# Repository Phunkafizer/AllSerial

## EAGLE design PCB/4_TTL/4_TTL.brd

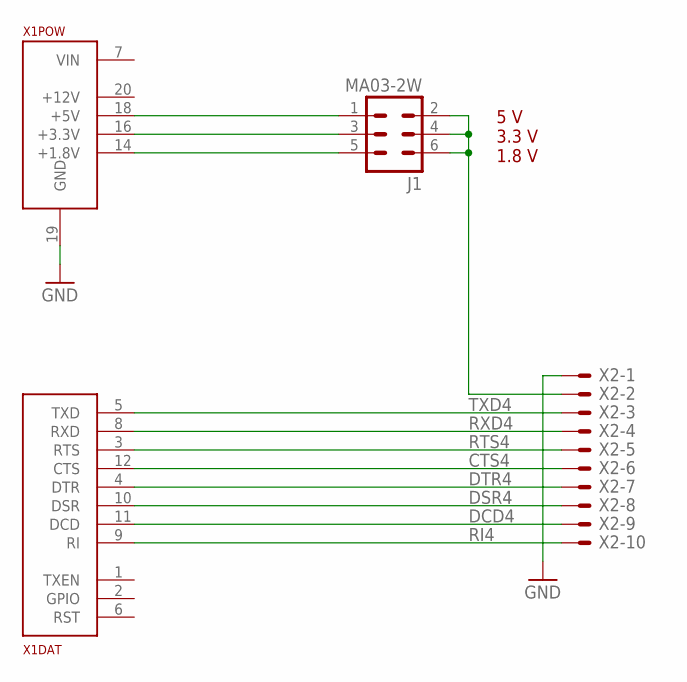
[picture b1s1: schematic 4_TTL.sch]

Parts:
J1: MA03-2W
X1: ALLSERIALD; DAUGHTER-THT
X2: AKL18X-10W; AKL182-10

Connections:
CTS4: X1.12 (CTS), X2.P$6
DCD4: X1.11 (DCD), X2.P$9
DSR4: X1.10 (DSR), X2.P$8
DTR4: X1.4 (DTR), X2.P$7
GND: X1.19 (GND), X2.P$1
unnamed: J1.2, J1.4, J1.6, X2.P$2
unnamed: J1.5, X1.14 (+1.8V)
unnamed: J1.3, X1.16 (+3.3V)
unnamed: J1.1, X1.18 (+5V)
RI4: X1.9 (RI), X2.P$10
RTS4: X1.3 (RTS), X2.P$5
RXD4: X1.8 (RXD), X2.P$4
TXD4: X1.5 (TXD), X2.P$3

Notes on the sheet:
5 V 3.3 V 1.8 V

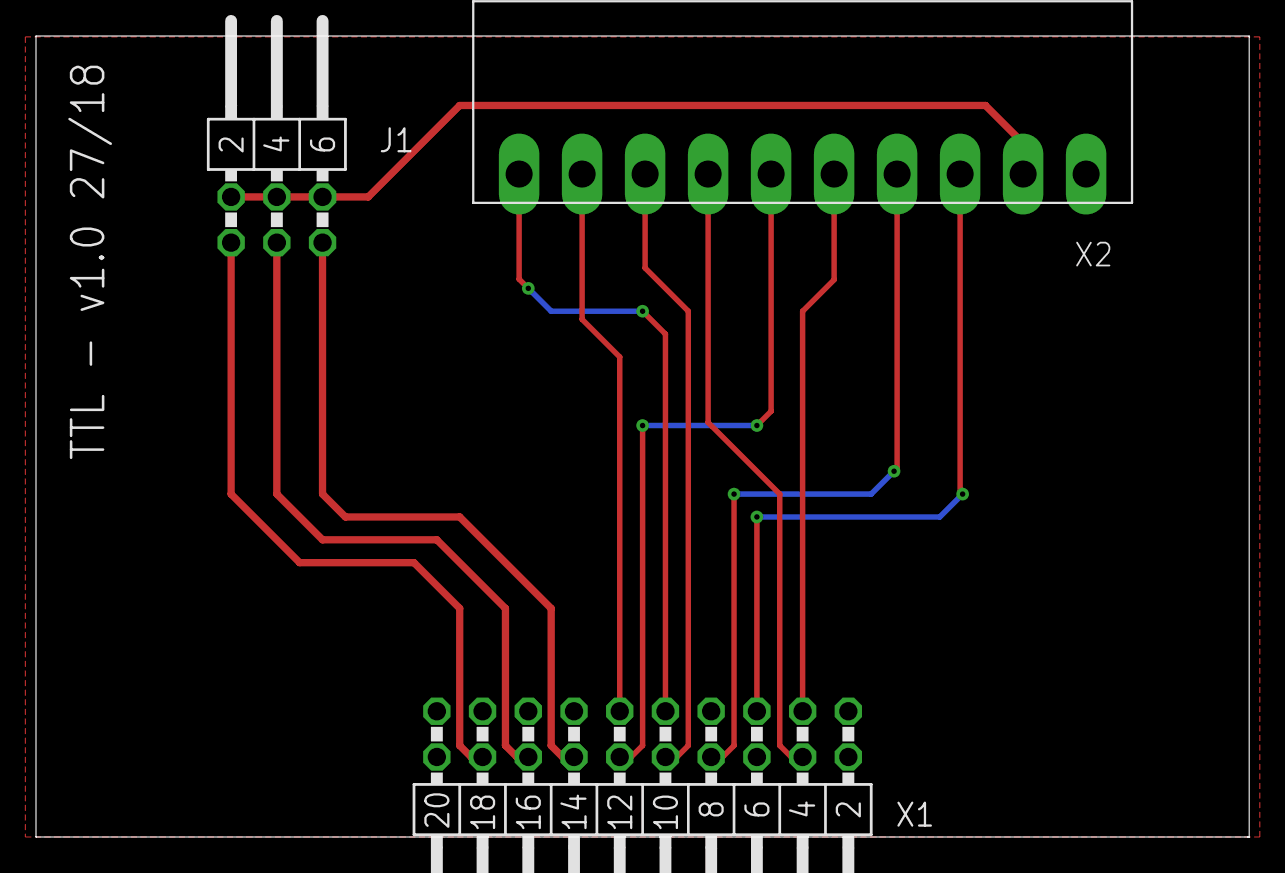
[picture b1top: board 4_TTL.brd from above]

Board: 2 copper layers, 67.4 x 44.5 mm, 3 parts (0 on the bottom side), 13 nets.

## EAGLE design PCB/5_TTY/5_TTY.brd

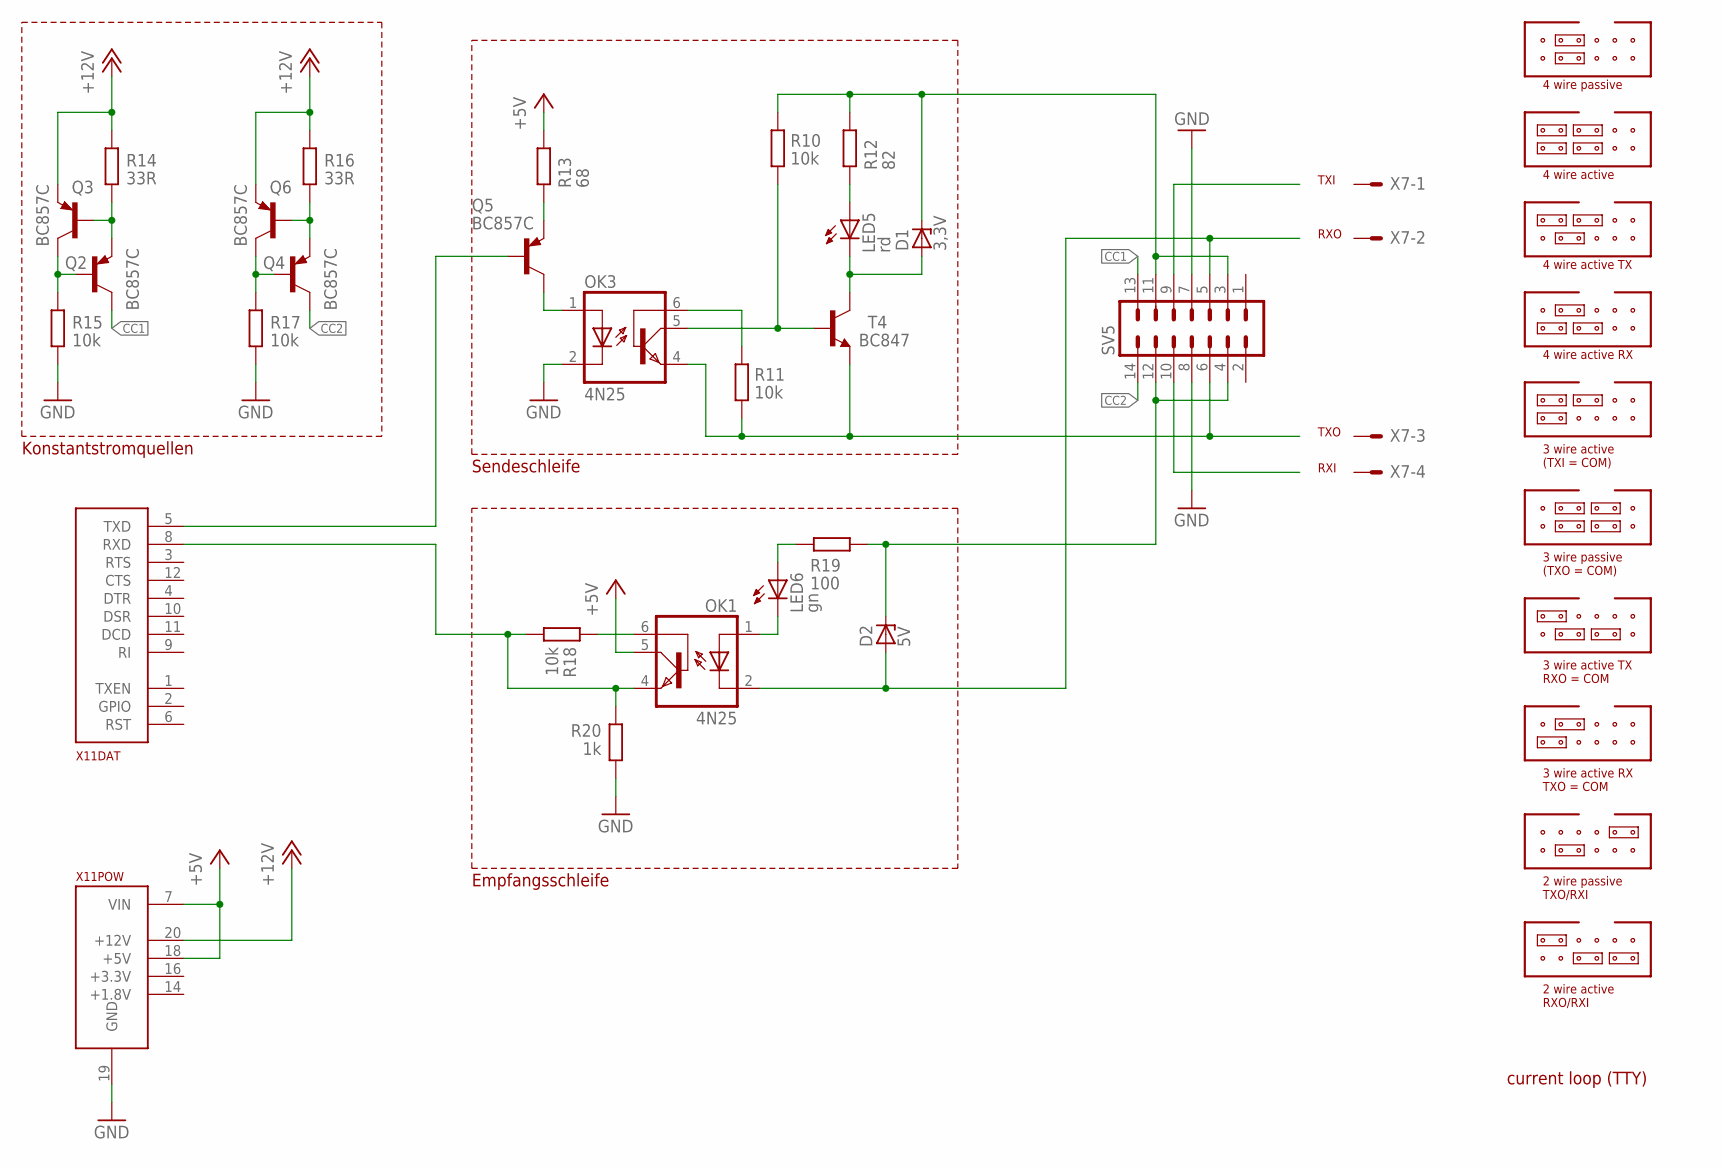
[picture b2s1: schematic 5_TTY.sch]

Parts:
D1: 3,3V; SOT23
D2: 5V; SOT23
LED5: rd; CHIPLED_0603
LED6: gn; CHIPLED_0603
OK1, OK3: 4N25; DIL06; FARNELL 1612454
Q2, Q3, Q4, Q5, Q6: BC857C; SOT23-BEC; FARNELL 8734771
R10, R11, R18: 10k; R0805; FARNELL 2498051
R12: 82; R0805; FARNELL 2498057
R13: 68; R0805; FARNELL 2498057
R14, R16: 33R; R0805; FARNELL 2498090
R15, R17: 10k; R0805; FARNELL 2502672
R19: 100; R0805; FARNELL 2498057
R20: 1k; R0805; FARNELL 2498050
SV5: ML14L
T4: BC847; SOT23; FARNELL 1081230
X7: AKL18X-04W; AKL182-04
X11: ALLSERIALD; DAUGHTER-THT

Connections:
+5V: OK1.5 (COL), R13.1, X11.7 (VIN), X11.18 (+5V)
+12V: Q3.E, Q6.E, R14.1, R16.1, X11.20 (+12V)
CC1: Q2.C, SV5.13
CC2: Q4.C, SV5.14
GND: OK3.2 (C), R15.1, R17.1, R20.1, SV5.7, SV5.8, X11.19 (GND)
unnamed: Q4.B, Q6.C, R17.2
unnamed: OK1.4 (EMI), R18.2, R20.2, X11.8 (RXD)
unnamed: Q4.E, Q6.B, R16.2
unnamed: OK3.6 (BAS), R11.1
unnamed: OK3.5 (COL), R10.2, T4.1 (B)
unnamed: D1.1 (A), LED5.C, T4.3 (C)
unnamed: Q2.B, Q3.C, R15.2
unnamed: LED5.A, R12.2
unnamed: Q2.E, Q3.B, R14.2
unnamed: OK3.1 (A), Q5.C
unnamed: Q5.E, R13.2
unnamed: OK1.6 (BAS), R18.1
unnamed: LED6.C, OK1.1 (A)
unnamed: LED6.A, R19.2
unnamed: Q5.B, X11.5 (TXD)
RXN: D2.1 (A), OK1.2 (C), SV5.5
RXP: D2.3 (C), R19.1, SV5.4, SV5.12
TXN: OK3.4 (EMI), R11.2, SV5.6, T4.2 (E)
TXP: D1.3 (C), R10.1, R12.1, SV5.3, SV5.11

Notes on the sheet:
4 wire passive
current loop (TTY)
TXI
TXO
4 wire active
RXO
RXI
4 wire active TX
4 wire active RX
2 wire active RXO/RXI
3 wire active (TXI = COM)
3 wire passive (TXO = COM)
3 wire active TX RXO = COM
Konstantstromquellen
Empfangsschleife
Sendeschleife
3 wire active RX TXO = COM
2 wire passive TXO/RXI

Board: 2 copper layers, 27 parts (0 on the bottom side), 24 nets, no tracks yet.

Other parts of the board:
U$7: 1296.2012

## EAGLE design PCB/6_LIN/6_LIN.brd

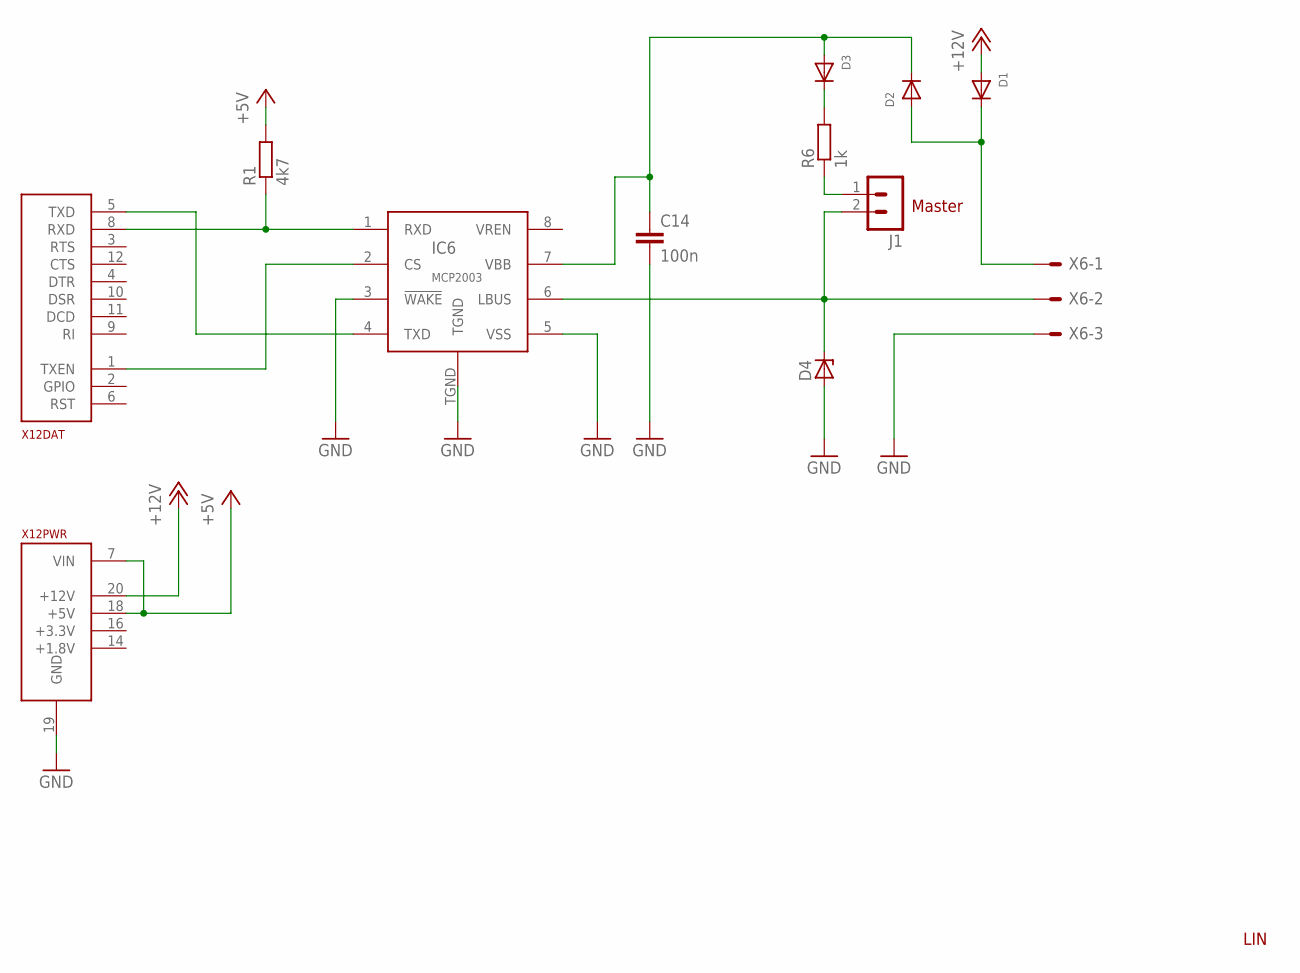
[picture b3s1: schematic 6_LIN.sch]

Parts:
C14: 100n; C0805
D1, D2, D3: DIODESOD-123; SOD-123
D4: ZENER-DIODESOT23; SOT23
IC6: MCP2003; SOIC8T
J1: MA02-1W; MA02-W
R1: 4k7; R0805
R6: 1k; R0805
X6: AKL18X-03W; AKL182-03
X12: ALLSERIALD; DAUGHTER-THT

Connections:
+5V: R1.2, X12.7 (VIN), X12.18 (+5V)
+12V: D1.A, X12.20 (+12V)
GND: C14.2, D4.1 (A), IC6.3 (!WAKE), IC6.5 (VSS), IC6.TGND, X6.P$3, X12.19 (GND)
unnamed: D1.C, D2.A, X6.P$1
unnamed: C14.1, D2.C, D3.A, IC6.7 (VBB)
unnamed: D4.3 (C), IC6.6 (LBUS), J1.2, X6.P$2
unnamed: J1.1, R6.1
unnamed: D3.C, R6.2
unnamed: IC6.4 (TXD), X12.5 (TXD)
unnamed: IC6.2 (CS), X12.1 (TXEN)
unnamed: IC6.1 (RXD), R1.1, X12.8 (RXD)

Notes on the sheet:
LIN
Master

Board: 2 copper layers, 11 parts (0 on the bottom side), 11 nets, no tracks yet.

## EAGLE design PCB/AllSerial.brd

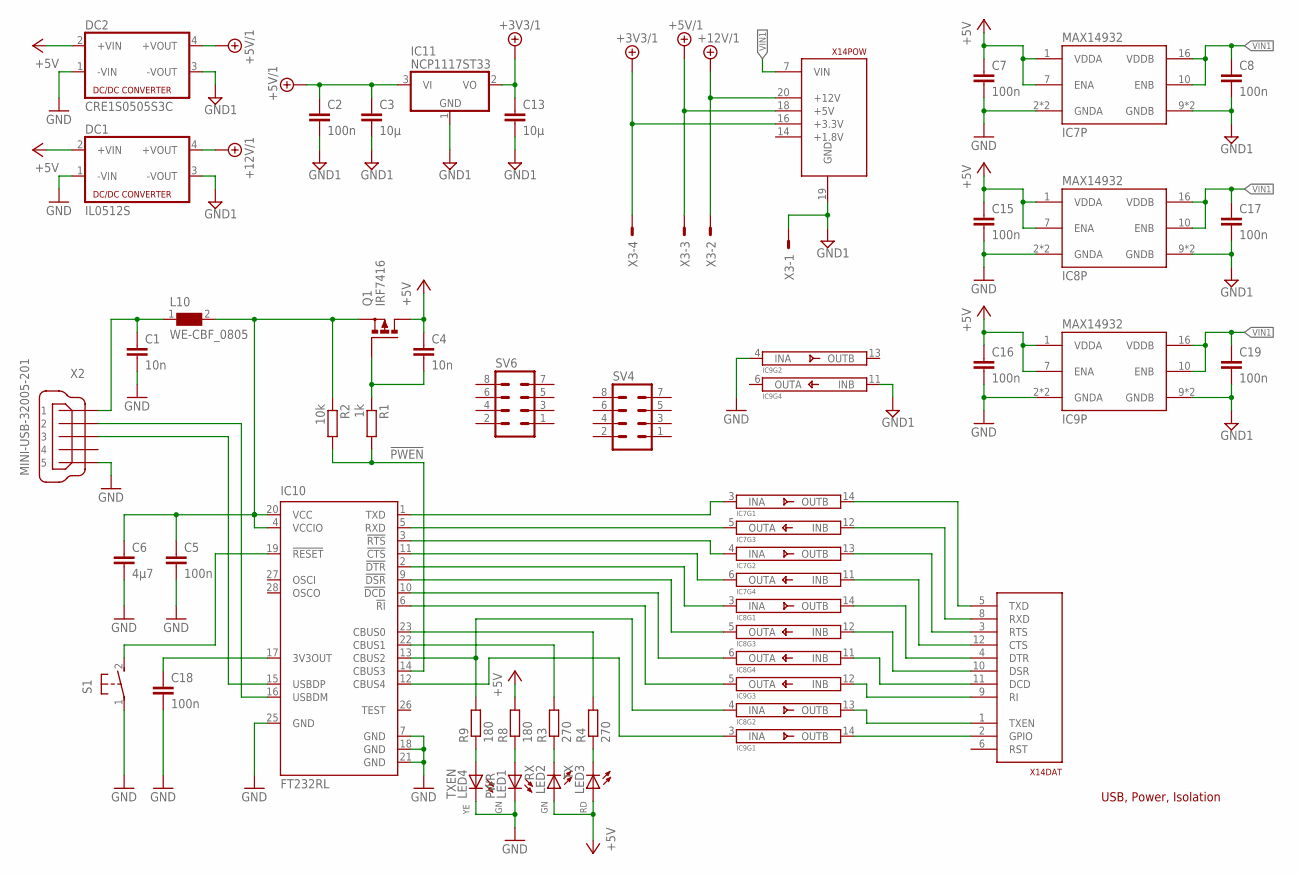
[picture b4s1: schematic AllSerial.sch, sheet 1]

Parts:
C1, C4: 10n; C0805
C2, C5, C7, C8, C15, C16, C17, C18, C19: 100n; C0805
C3, C13: 10µ; C0805
C6: 4µ7; C0805
DC1: IL0512S; NME
DC2: CRE1S0505S3C; NME
IC7, IC8, IC9: MAX14932; SO16
IC10: FT232RL; SSOP28
IC11: NCP1117ST33; SOT23
L10: WE-CBF_0805; 0805
LED1: PWR; CHIPLED_0805
LED2: RX; CHIPLED_0805
LED3: TX; CHIPLED_0805
LED4: TXEN; CHIPLED_0805
Q1: IRF7416; SO-08
R1: 1k; R0805
R2: 10k; R0805
R3, R4: 270; R0805
R8, R9: 180; R0805
S1: 31-XX; B3F-31XX
SV4, SV6: MA04-2
X2: MINI-USB-32005-201; 32005-201
X3: AKL18X-04W; AKL182-04
X14: ALLSERIALMM; MAIN-THT

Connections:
!PWEN: IC10.14 (CBUS3), R1.2, R2.2
+3V3/1: C13.1, IC11.2 (VO), X3.P$4, X14.16 (+3.3V)
+5V: C4.1, C7.1, C15.1, C16.1, DC1.2 (+VIN), DC2.2 (+VIN), IC7.1 (VDDA), IC7.7 (ENA), IC8.1 (VDDA), IC8.7 (ENA), IC9.1 (VDDA), IC9.7 (ENA), LED2.A, LED3.A, Q1.5 (D), Q1.6 (D), Q1.7 (D), Q1.8 (D), R8.2
+5V/1: C2.1, C3.1, DC2.4 (+VOUT), IC11.3 (VI), X3.P$3, X14.18 (+5V)
+12V/1: DC1.4 (+VOUT), X3.P$2, X14.20 (+12V)
GND: C1.2, C5.2, C6.2, C7.2, C15.2, C16.2, C18.2, DC1.1 (-VIN), DC2.1 (-VIN), IC7.2 (GNDA), IC7.8 (GNDA), IC8.2 (GNDA), IC8.8 (GNDA), IC9.2 (GNDA), IC9.4 (INA), IC9.8 (GNDA), IC10.7 (GND), IC10.18 (GND), IC10.21 (GND), IC10.25 (GND), LED1.C, LED4.C, S1.1, X2.5
GND1: C2.2, C3.2, C8.2, C13.2, C17.2, C19.2, DC1.3 (-VOUT), DC2.3 (-VOUT), IC7.9 (GNDB), IC7.15 (GNDB), IC8.9 (GNDB), IC8.15 (GNDB), IC9.9 (GNDB), IC9.11 (INB), IC9.15 (GNDB), IC11.1 (GND), X3.P$1, X14.19 (GND)
unnamed: IC8.4 (INA), IC10.13 (CBUS2), R9.2
unnamed: LED3.C, R4.1
unnamed: IC10.19 (!RESET), S1.2 (S)
unnamed: LED2.C, R3.1
unnamed: LED4.A, R9.1
unnamed: LED1.A, R8.1
unnamed: C1.1, L10.1, X2.1
unnamed: IC9.3 (INA), IC10.12 (CBUS4)
unnamed: IC7.3 (INA), IC10.1 (TXD)
unnamed: IC10.16 (USBDM), X2.2
unnamed: IC7.5 (OUTA), IC10.5 (RXD)
unnamed: IC10.15 (USBDP), X2.3
unnamed: C18.1, IC10.17 (3V3OUT)
unnamed: IC7.4 (INA), IC10.3 (!RTS)
unnamed: IC7.6 (OUTA), IC10.11 (!CTS)
unnamed: IC8.3 (INA), IC10.2 (!DTR)
unnamed: IC8.5 (OUTA), IC10.9 (!DSR)
unnamed: IC8.6 (OUTA), IC10.10 (!DCD)
unnamed: IC9.5 (OUTA), IC10.6 (!RI)
unnamed: C5.1, C6.1, IC10.4 (VCCIO), IC10.20 (VCC), L10.2, Q1.1 (S), Q1.2 (S), Q1.3 (S), R2.1
unnamed: C4.2, Q1.4 (G), R1.1
unnamed: IC7.14 (OUTB), X14.5 (TXD)
unnamed: IC7.12 (INB), X14.8 (RXD)
unnamed: IC7.13 (OUTB), X14.3 (RTS)
unnamed: IC7.11 (INB), X14.12 (CTS)
unnamed: IC8.14 (OUTB), X14.4 (DTR)
unnamed: IC8.12 (INB), X14.10 (DSR)
unnamed: IC8.11 (INB), X14.11 (DCD)
unnamed: IC9.12 (INB), X14.9 (RI)
unnamed: IC8.13 (OUTB), X14.1 (TXEN)
unnamed: IC9.14 (OUTB), X14.2 (GPIO)
RXLED: IC10.22 (CBUS1), R3.2
TXLED: IC10.23 (CBUS0), R4.2
VIN1: C8.1, C17.1, C19.1, IC7.10 (ENB), IC7.16 (VDDB), IC8.10 (ENB), IC8.16 (VDDB), IC9.10 (ENB), IC9.16 (VDDB), X14.7 (VIN)

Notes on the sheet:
USB, Power, Isolation

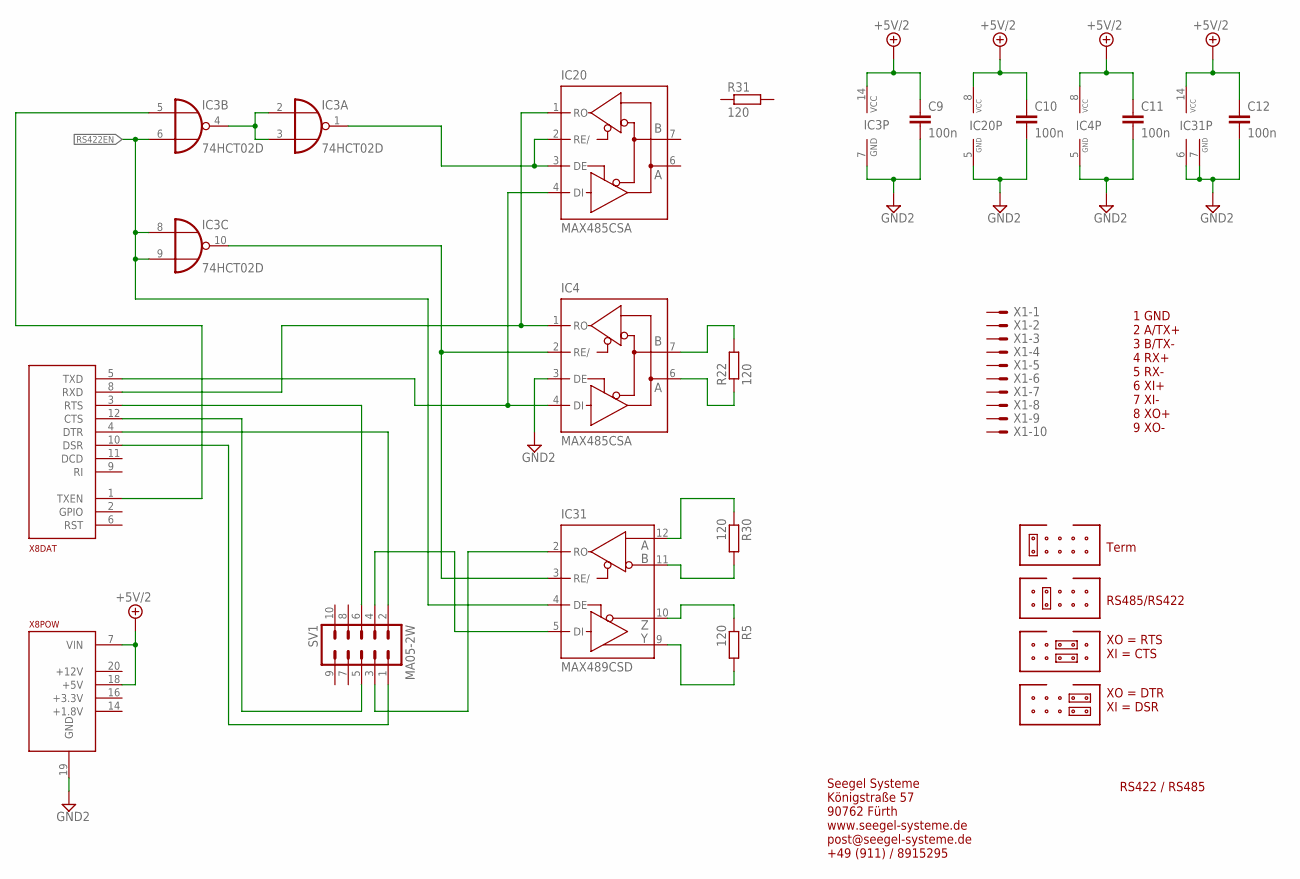
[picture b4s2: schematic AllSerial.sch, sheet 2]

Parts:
C9, C10, C11, C12: 100n; C0805
IC3: 74HCT02D; SO14
IC4, IC20: MAX485CSA; SO08
IC31: MAX489CSD; SO14
R5, R22, R30, R31: 120; R0805
SV1: MA05-2W
X1: AKL18X-10W; AKL182-10
X8: ALLSERIALD; DAUGHTER-THT

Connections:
+5V/2: C9.1, C10.1, C11.1, C12.1, IC3.14 (VCC), IC4.8 (VCC), IC20.8 (VCC), IC31.14 (VCC), X8.7 (VIN), X8.18 (+5V)
GND2: C9.2, C10.2, C11.2, C12.2, IC3.7 (GND), IC4.3 (DE), IC4.5 (GND), IC20.5 (GND), IC31.6 (GND), IC31.7 (GND), X8.19 (GND)
unnamed: IC31.11 (B), R30.2
unnamed: IC31.10 (Z), R5.1
unnamed: IC31.9 (Y), R5.2
unnamed: IC3.5 (I0), X8.1 (TXEN)
unnamed: IC31.12 (A), R30.1
unnamed: SV1.5, X8.12 (CTS)
unnamed: IC4.7 (B), R22.2
unnamed: IC4.6 (A), R22.1
unnamed: IC3.2 (I0), IC3.3 (I1), IC3.4 (O)
unnamed: IC3.1 (O), IC20.2 (RE/), IC20.3 (DE)
unnamed: IC3.10 (O), IC4.2 (RE/), IC31.3 (RE/)
unnamed: IC4.1 (RO), IC20.1 (RO), X8.8 (RXD)
unnamed: IC4.4 (DI), IC20.4 (DI), X8.5 (TXD)
unnamed: SV1.6, X8.3 (RTS)
unnamed: SV1.2, X8.4 (DTR)
unnamed: IC31.5 (DI), SV1.4
unnamed: IC31.2 (RO), SV1.3
unnamed: SV1.1, X8.10 (DSR)
RS422EN: IC3.6 (I1), IC3.8 (I0), IC3.9 (I1), IC31.4 (DE)

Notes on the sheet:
Seegel Systeme Königstraße 57 90762 Fürth www.seegel-systeme.de post@seegel-systeme.de +49 (911) / 8915295
RS422 / RS485
Term
RS485/RS422
XO = RTS XI = CTS
XO = DTR XI = DSR
1 GND 2 A/TX+ 3 B/TX- 4 RX+ 5 RX- 6 XI+ 7 XI- 8 XO+ 9 XO-

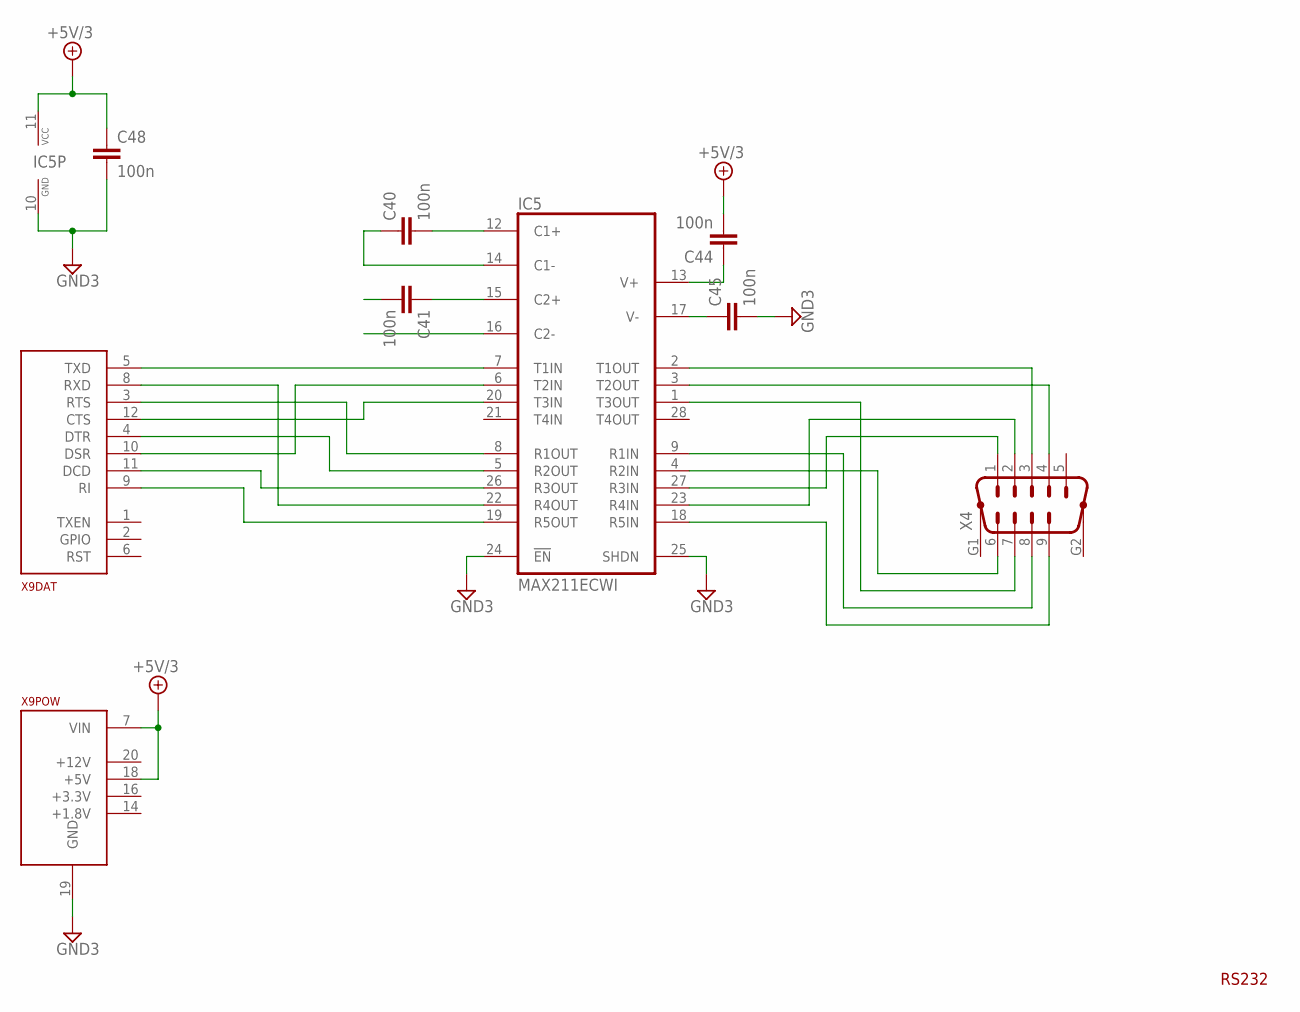
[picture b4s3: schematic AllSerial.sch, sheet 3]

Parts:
C40, C41, C44, C45, C48: 100n; C0805
IC5: MAX211ECWI; SO28L
X4: M09HP
X9: ALLSERIALD; DAUGHTER-THT

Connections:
+5V/3: C44.2, C48.1, IC5.11 (VCC), X9.7 (VIN), X9.18 (+5V)
GND3: C45.2, C48.2, IC5.10 (GND), IC5.24 (EN), IC5.25 (SHDN), X9.19 (GND)
unnamed: IC5.18 (R5IN), X4.9
unnamed: IC5.9 (R1IN), X4.8
unnamed: IC5.1 (T3OUT), X4.7
unnamed: IC5.4 (R2IN), X4.6
unnamed: IC5.27 (R3IN), X4.1
unnamed: IC5.23 (R4IN), X4.2
unnamed: IC5.2 (T1OUT), X4.3
unnamed: IC5.3 (T2OUT), X4.4
unnamed: C40.2, IC5.12 (C1+)
unnamed: C40.1, IC5.14 (C1-)
unnamed: C41.1, IC5.15 (C2+)
unnamed: C45.1, IC5.17 (V-)
unnamed: C44.1, IC5.13 (V+)
unnamed: IC5.7 (T1IN), X9.5 (TXD)
unnamed: IC5.22 (R4OUT), X9.8 (RXD)
unnamed: IC5.20 (T3IN), X9.12 (CTS)
unnamed: IC5.8 (R1OUT), X9.3 (RTS)
unnamed: IC5.26 (R3OUT), X9.11 (DCD)
unnamed: IC5.19 (R5OUT), X9.9 (RI)
unnamed: IC5.5 (R2OUT), X9.4 (DTR)
unnamed: IC5.6 (T2IN), X9.10 (DSR)

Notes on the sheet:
RS232

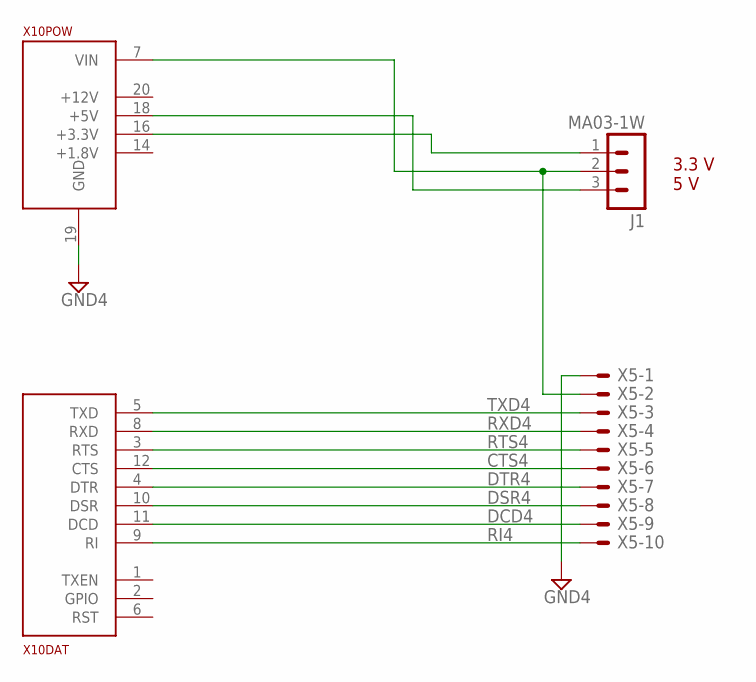
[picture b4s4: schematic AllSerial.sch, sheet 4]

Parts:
J1: MA03-1W
X5: AKL18X-10W; AKL182-10
X10: ALLSERIALD; DAUGHTER-THT

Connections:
CTS4: X5.P$6, X10.12 (CTS)
DCD4: X5.P$9, X10.11 (DCD)
DSR4: X5.P$8, X10.10 (DSR)
DTR4: X5.P$7, X10.4 (DTR)
GND4: X5.P$1, X10.19 (GND)
unnamed: J1.1, X10.16 (+3.3V)
unnamed: J1.3, X10.18 (+5V)
unnamed: J1.2, X5.P$2, X10.7 (VIN)
RI4: X5.P$10, X10.9 (RI)
RTS4: X5.P$5, X10.3 (RTS)
RXD4: X5.P$4, X10.8 (RXD)
TXD4: X5.P$3, X10.5 (TXD)

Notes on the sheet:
3.3 V 5 V

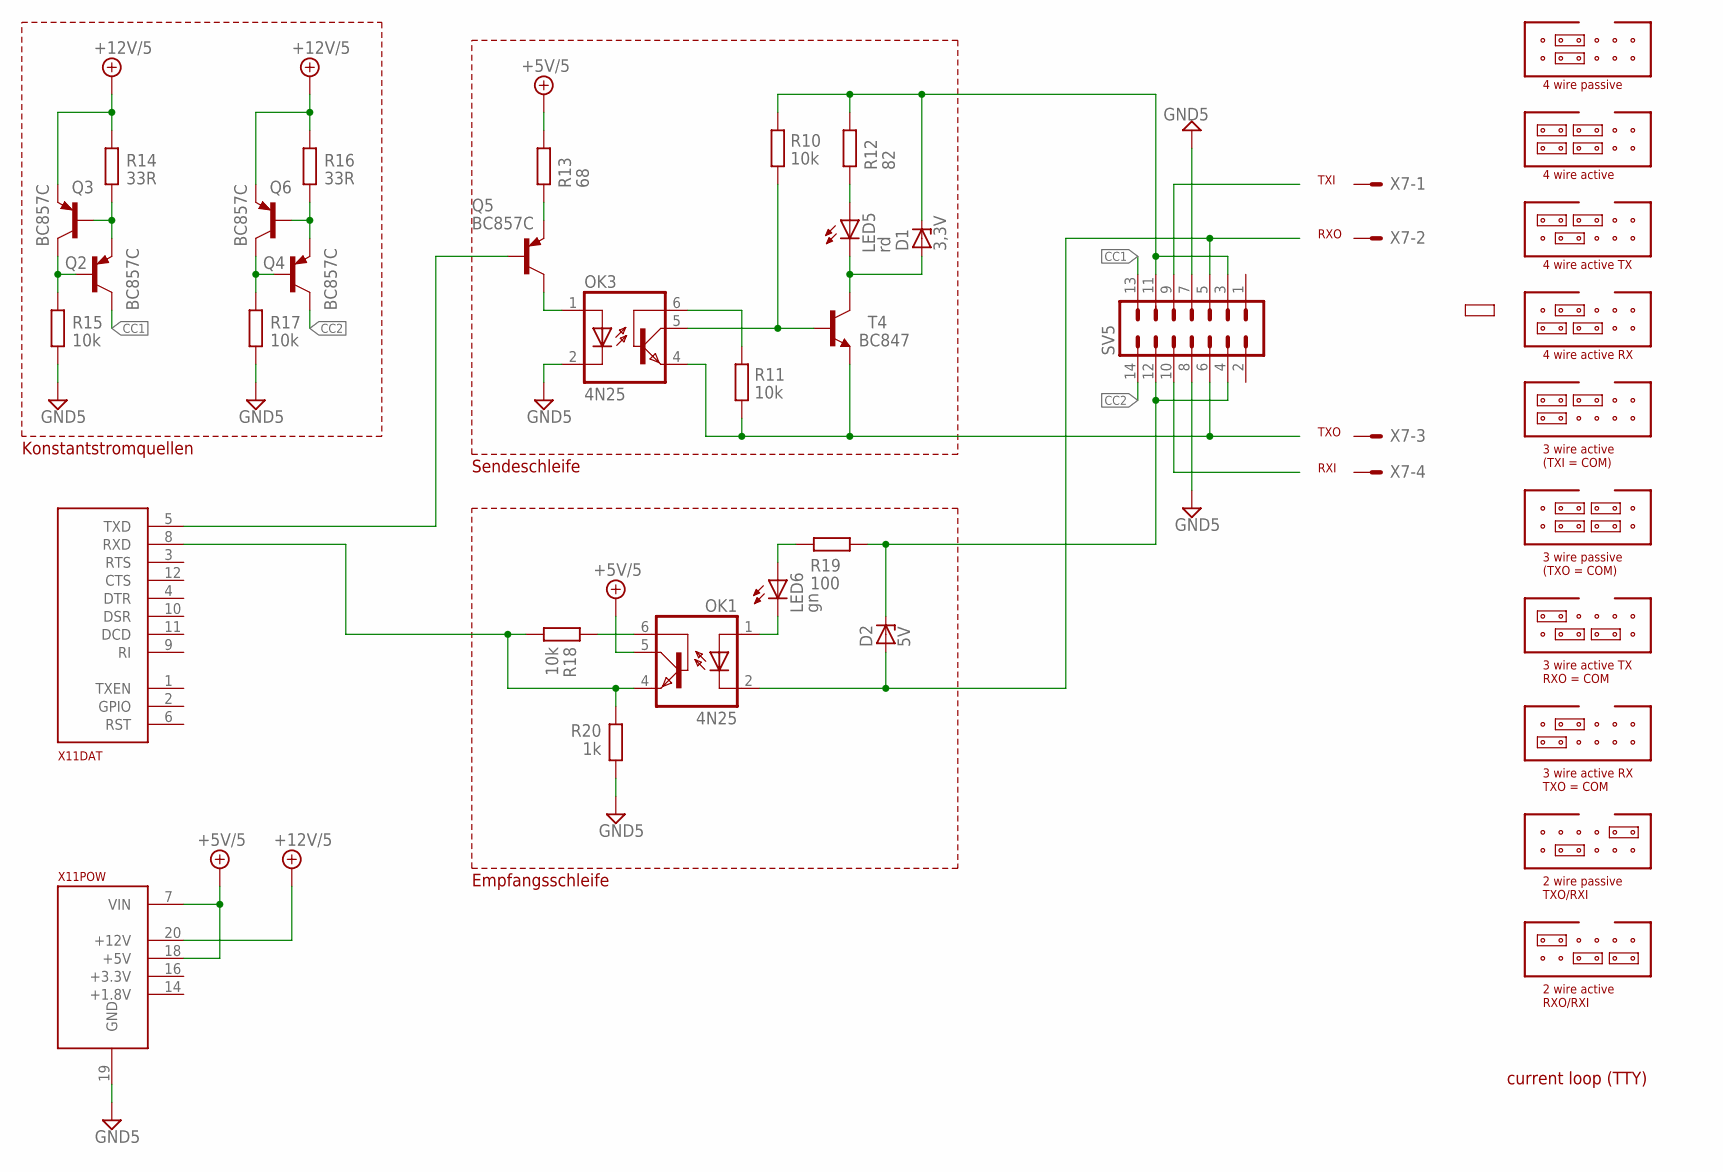
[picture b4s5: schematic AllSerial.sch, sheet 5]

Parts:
D1: 3,3V; SOT23
D2: 5V; SOT23
LED5: rd; CHIPLED_0603
LED6: gn; CHIPLED_0603
OK1, OK3: 4N25; DIL06; FARNELL 1612454
Q2, Q3, Q4, Q5, Q6: BC857C; SOT23-BEC; FARNELL 8734771
R10, R11, R18: 10k; R0805; FARNELL 2498051
R12: 82; R0805; FARNELL 2498057
R13: 68; R0805; FARNELL 2498057
R14, R16: 33R; R0805; FARNELL 2498090
R15, R17: 10k; R0805; FARNELL 2502672
R19: 100; R0805; FARNELL 2498057
R20: 1k; R0805; FARNELL 2498050
SV5: ML14L
T4: BC847; SOT23; FARNELL 1081230
X7: AKL18X-04W; AKL182-04
X11: ALLSERIALD; DAUGHTER-THT

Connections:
+5V/5: OK1.5 (COL), R13.1, X11.7 (VIN), X11.18 (+5V)
+12V/5: Q3.E, Q6.E, R14.1, R16.1, X11.20 (+12V)
CC1: Q2.C, SV5.13
CC2: Q4.C, SV5.14
GND5: OK3.2 (C), R15.1, R17.1, R20.1, SV5.7, SV5.8, X11.19 (GND)
unnamed: Q4.B, Q6.C, R17.2
unnamed: OK1.4 (EMI), R18.2, R20.2, X11.8 (RXD)
unnamed: Q4.E, Q6.B, R16.2
unnamed: OK3.6 (BAS), R11.1
unnamed: OK3.5 (COL), R10.2, T4.1 (B)
unnamed: D1.1 (A), LED5.C, T4.3 (C)
unnamed: Q2.B, Q3.C, R15.2
unnamed: LED5.A, R12.2
unnamed: Q2.E, Q3.B, R14.2
unnamed: OK3.1 (A), Q5.C
unnamed: Q5.E, R13.2
unnamed: OK1.6 (BAS), R18.1
unnamed: LED6.C, OK1.1 (A)
unnamed: LED6.A, R19.2
unnamed: Q5.B, X11.5 (TXD)
RXN: D2.1 (A), OK1.2 (C), SV5.5
RXP: D2.3 (C), R19.1, SV5.4, SV5.12
TXN: OK3.4 (EMI), R11.2, SV5.6, T4.2 (E)
TXP: D1.3 (C), R10.1, R12.1, SV5.3, SV5.11

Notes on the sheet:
4 wire passive
current loop (TTY)
TXI
TXO
4 wire active
RXO
RXI
4 wire active TX
4 wire active RX
2 wire active RXO/RXI
3 wire active (TXI = COM)
3 wire passive (TXO = COM)
3 wire active TX RXO = COM
Konstantstromquellen
Empfangsschleife
Sendeschleife
3 wire active RX TXO = COM
2 wire passive TXO/RXI

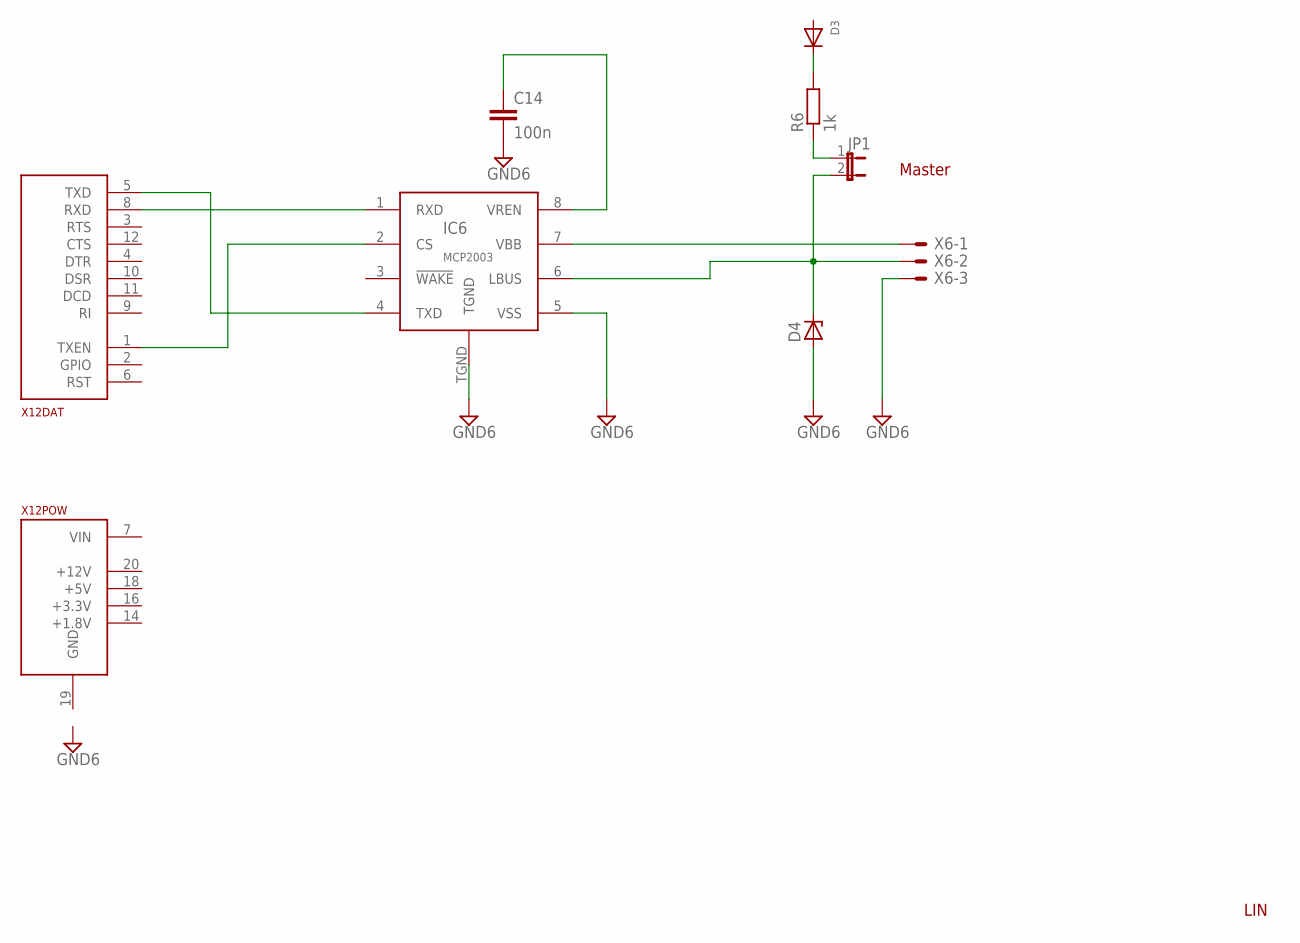
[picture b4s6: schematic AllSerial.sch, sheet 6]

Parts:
C14: 100n; C0805
D3: DIODESOD-123; SOD-123
D4: ZENER-DIODESOT23; SOT23
IC6: MCP2003; SOIC8T
JP1: JP1E; JP1
R6: 1k; R0805
X6: AKL18X-03W; AKL182-03
X12: ALLSERIALD; DAUGHTER-THT

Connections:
GND6: C14.2, D4.1 (A), IC6.5 (VSS), IC6.TGND, X6.P$3
unnamed: IC6.7 (VBB), X6.P$1
unnamed: D4.3 (C), IC6.6 (LBUS), JP1.2, X6.P$2
unnamed: JP1.1, R6.1
unnamed: D3.C, R6.2
unnamed: C14.1, IC6.8 (VREN)
unnamed: IC6.4 (TXD), X12.5 (TXD)
unnamed: IC6.2 (CS), X12.1 (TXEN)
unnamed: IC6.1 (RXD), X12.8 (RXD)

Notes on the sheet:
LIN
Master

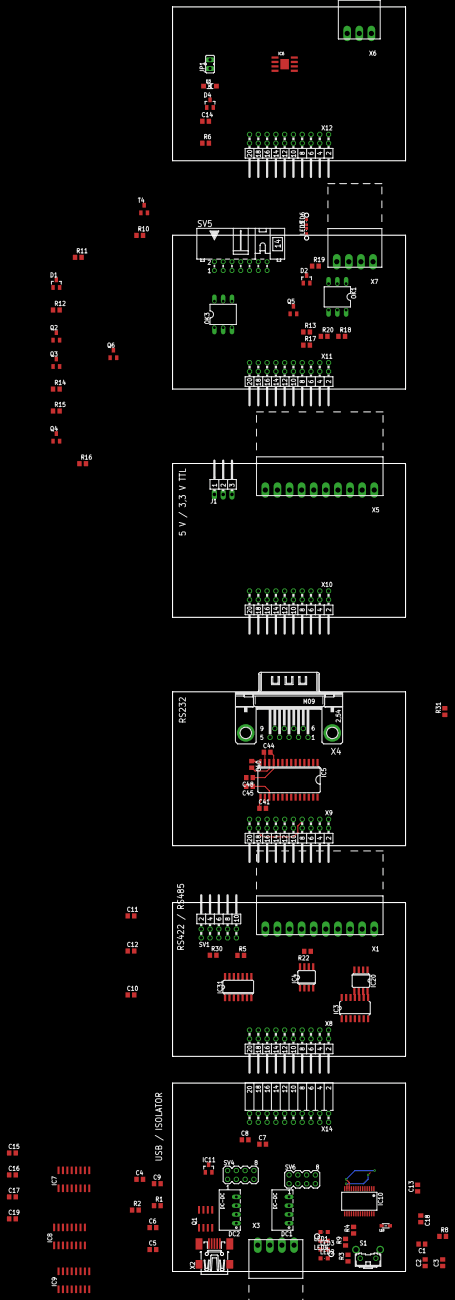
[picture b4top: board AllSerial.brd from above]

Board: 2 copper layers, 101 parts (0 on the bottom side), 130 nets.

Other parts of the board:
U$3: 1296.1004
U$7: 1296.2012

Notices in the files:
parts and their libraries:
microbuilder: This work is placed in the public domain, and may be freely used for commercial and non-commercial work with the following conditions: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
EagleLibrary_Wuerth_Elektronik_eiSos_Ver: Copyright: Würth Elektronik
